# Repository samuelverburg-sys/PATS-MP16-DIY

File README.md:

# PATS MP-16 DIY kit

A 16-pad MIDI chord controller you build yourself: 16 MX pads and a Shift key with RGB lighting, a
rotary encoder, a 128x64 OLED, USB MIDI and 3.5 mm TRS MIDI In and Out. By
[PATS audio](https://patsaudio.com/).

This repository holds rev 2 of the kit and the firmware for both revisions:

| | Rev 1 (original kit) | Rev 2 (this repo) |
|---|---|---|
| MCU | Waveshare RP2040-Zero module | RP2040 on the board, 16 MB flash, USB-C |
| Keys | 4x4 matrix + Shift on its own pin | 3x 74HC165 shift registers: every key on its own input, no ghosting |
| Power | LiPo, MCP73831 charger | LiPo with power path (plays while charging), reverse-polarity protection, battery voltage sense, 5 V LED supply |
| MIDI | TRS In + Out | TRS In + Out (Type A), Thru selectable in the MIDI menu |
| Expansion | 3-pin header | 4-pin I2C connector (JST SH, Qwiic / STEMMA QT pinout) for add-on boards |

The rev 1 manual (printing, assembly, how the Chordmaker works):
[PATS MP-16 DIY Kit Manual](https://docs.google.com/document/d/1Koq2ymRy1WZg_HTG9N3nUoAihR9oNaCTS2vanQYqxgY/).

## Firmware

| Sketch | What it does | USB stack |
|---|---|---|
| `MP16_Chordmaker` | The main firmware: each pad plays a chord in the chosen key and scale | Adafruit TinyUSB |
| `MP16_Boilerplate` | Starting point for your own firmware | Adafruit TinyUSB |
| `MP16_YoutubeKeyboard` | The MP-16 as a USB keyboard for YouTube shortcuts | Pico SDK |

### With the Arduino IDE

1. Install the "Raspberry Pi Pico/RP2040/RP2350" boards (Boards Manager; from
   [arduino-pico](https://github.com/earlephilhower/arduino-pico)).
2. Install the libraries Adafruit NeoPixel, Adafruit SSD1306 and Adafruit GFX (Library Manager).
3. **File > Preferences > Sketchbook location**: the `firmware` folder of this repository. The IDE then
   finds the sketches (File > Sketchbook) and the `MP16` library they share.
4. Pick the board and options:

   | | Rev 1 kit | Rev 2 kit |
   |---|---|---|
   | Board | Waveshare RP2040 Zero | Generic RP2040 |
   | Flash Size | 2MB (Sketch: 1536KB, FS: 512KB) | 16MB (Sketch: 2MB, FS: 14MB) |
   | Boot Stage 2 | (default) | W25Q080 QSPI /2 |
   | USB Stack | as in the table above | as in the table above |

   The firmware picks the right pins from the board you choose.
5. Hold **BOOT**, press and release **RESET**, release BOOT: the MP-16 appears as a drive. Click Upload.

### With the command line

```sh
scripts/setup-arduino.sh        # pinned arduino-cli, RP2040 core and libraries
scripts/build-firmware.sh       # every sketch for both boards: build/<rev>/<sketch>/<sketch>.ino.uf2
make -C firmware/test           # tests of the chord engine, MIDI parser and input logic (needs g++)
```

Copy the `.uf2` onto the MP-16's drive (BOOT + RESET as above) to flash it.

## Hardware

The rev 2 schematic and PCB are generated from `hardware/mp16/design.py` with KiCad 7+ and
Freerouting (`hardware/README.md`). The generated KiCad project and the JLCPCB order files are in
`hardware/mp16/`. The original rev 1 EasyEDA project is in `hardware/reference/`.

## Enclosure

`enclosure/stl/`: Top, Midplate, Bottom (closed or open), Switch and OLED standoff, the same for both
revisions. `enclosure/layout.kle.json` is the key layout for
[keyboard-layout-editor.com](http://www.keyboard-layout-editor.com/).

## Working on this with Claude

`CLAUDE.md` describes the layout, commands and rules; cloud sessions install the toolchain through
`.claude/hooks/session-start.sh`. Other firmware for the kit:
[MP-16 Chordmaker V2](https://github.com/giusmarci/MP16-CHORDMAKER-V2) by @giusmarci.

Questions, builds and ideas: [PATS audio on Instagram](https://www.instagram.com/patsaudio/).

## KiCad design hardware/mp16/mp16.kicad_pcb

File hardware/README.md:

# MP-16 rev 2 hardware

One board, generated from Python and checked by script: `mp16/design.py` is the source of truth for
every part, value, LCSC number, connection and position. The KiCad files in `mp16/` are generated from
it; never edit them by hand (the next build overwrites them).

| | |
|---|---|
| Outline | 76.2 x 104.775 mm, six 2.5 mm holes: the rev-1 board, so the enclosure (`../enclosure/stl/`) fits |
| Layers | 2, JLCPCB standard rules (0.127 mm tracks, 0.13 mm clearance) |
| Assembly | every SMD part on the bottom (one JLCPCB assembly side, as rev 1); 4 layers (In1 GND, In2 VLED; Samuel 2026-11-03: cheaper overall than 2 layers with double-sided assembly); hand-soldered on top: encoder, OLED header |
| Spec and decisions | `../docs/SPEC.md`, `../docs/decisions/` |

## Build

```sh
../scripts/setup-kicad.sh          # KiCad 7, Java 25, Freerouting 2.5.0 (once)
python3 build.py mp16 check        # netlist checks (seconds)
python3 build.py mp16 sch          # schematic + KiCad netlist round trip
python3 build.py mp16 pcb          # placed board + placement checks (courtyards, part drawings, facing, crossing order)
python3 build.py mp16 all          # check, sch, pcb, route, drc, review, fab (about 10 minutes)
python3 tools/where.py mp16 [x0 y0 x1 y1]   # part boxes in the design frame, for placing parts
BOARD=mp16 tools/xray.sh build/xray.png 250 [x0 y0 w h]   # bottom parts seen from above (design frame)
BOARD=mp16 tools/render.sh build   # top and bottom renders
python3 ../scripts/check-pins.py   # firmware pins (board_pins.h) == this board
```

Outputs: `mp16/mp16.kicad_sch`, `mp16/mp16.kicad_pcb`, `mp16/fab/` (Gerbers zip, BOM and CPL for
JLCPCB). Every `route`, `drc` and `review` run adds a line to `build-log.jsonl`.

## Where things are and why

Frame: mm seen from above, (0, 0) = top-left corner, y = 0 is the edge with the jacks (the KLE layout's
frame; the enclosure STLs use the same x and y_stl = 104.775 - y).

- **Fixed by the enclosure** (rev-1 positions, placed by `pin_targets` onto the rev-1 pad centres from
  `reference/rev1-pcb.easyeda.json`, with footprints converted from that board): MIDI In jack (x 19.6),
  USB-C (x 38.1, where the RP2040-Zero's socket was), MIDI Out jack (x 53.9), power switch (x 68.3),
  side-view charge LED, encoder, OLED header. These never move (Samuel, 2026-10-22). The battery plug
  (66.4, 26.7) is at its rev-1 position too, but may move.
  Checked against the STL openings with `tools/stl_openings.py`.
- **Top band (y 0-31)**: RP2040 and its flash and crystal in the middle (inside the window of the "Bottom
  (Open)" shell, with BOOT, RESET and the SWD pads), MIDI In circuit under its jack, charger, load switch,
  LDO and LED level shifter on the right, battery voltage divider and protection beside the battery plug.
  0402 passives here; 0603 elsewhere.
- **Buttons and debug**: BOOT (SW18) and RESET (SW19) side by side in the lower left of the open bottom
  shell's window, named on the bottom silkscreen; above them three SWD pads, TP2 SWDIO, TP1 SWCLK,
  TP3 GND (left to right seen from above, right to left seen from below). Flashing a blank or stuck
  board: hold BOOT, press RESET, release BOOT; the RPI-RP2 drive appears.
- **Key area**: hot-swap sockets, LEDs and their capacitors as the PATS UI board; U1 (pads 1-8) between key
  rows 1 and 2 and U2 (pads 9-16) between rows 3 and 4, next to the keys they read; the 5 V LED boost
  between pads 3 and 4 and along row 1's LEDs.

## JLCPCB (PCB and assembly)

The board is made and assembled at JLCPCB (Samuel, 2026-10-22). Check the numbers below against their
current capabilities page before each order; the build enforces the ones in **bold**.

| Constraint | JLCPCB (4-layer, standard) | This board |
|---|---|---|
| Track width / spacing | 0.127 / 0.127 mm minimum | **0.127 mm min track, 0.13 mm clearance** (router works to 0.15) |
| Vias | 0.3 mm drill / 0.6 mm pad without extra cost (0.2 mm possible at a fee) | **0.3 / 0.6 mm**, 0.4 / 0.8 mm on power |
| Copper to board edge | 0.3 mm | **0.3 mm** |
| Assembly sides | one side is cheapest (two sides = second setup) | **all SMD on the bottom** |
| Parts over the board edge | needs edge rails (JLCPCB adds them, small fee), as rev 1 | jacks, USB-C, power switch overhang the top edge, as rev 1 |
| Fine pitch | 0.4 mm QFN fine; ENIG recommended | RP2040 0.4 mm, BQ24074 0.5 mm, JST SH 1.0 mm |
| Parts library | basic parts free; each extended part type has a setup fee | `mp16/PARTS.md`; prefer basic passives |
| Through-hole | hand-soldered here (cheaper); JLCPCB THT assembly possible | encoder, OLED header, battery plug; USB-C's shell legs are through-hole but it is placed by JLCPCB (in the CPL) |
| Files | Gerber zip, BOM (Comment, Designator, Footprint, LCSC), CPL (Designator, Mid X/Y, Layer, Rotation) | `mp16/fab/` |

## Fit checks still open (before ordering)

1. USB-C height: the RP2040-Zero's socket sat 1 mm lower (on the module's own board); this socket is on
   the main board. The enclosure opening (about 16 x 10 mm) leaves ~0.5 mm above a standard plug. Check
   with the printed Top/Bottom and a real cable.
2. 3D check of the stack (PCB, plate, OLED, battery between board and bottom shell).

## Pipeline

`build.py`, `tools/` and `lib/` are copied from the PATS repository (github.com/samuelverburg-sys/PATS,
`pats-core/hardware/`, commit 3d1c7dc, 2026-10-22); `PATS-PIPELINE.md` lists the changes made here.
The routing approach (Freerouting in stages, then a local finish router and ground stitching) is
described in the PATS hardware README; this board routes the RP2040's 0.4 mm pins and the charger's
power pins first, then power, then everything else.

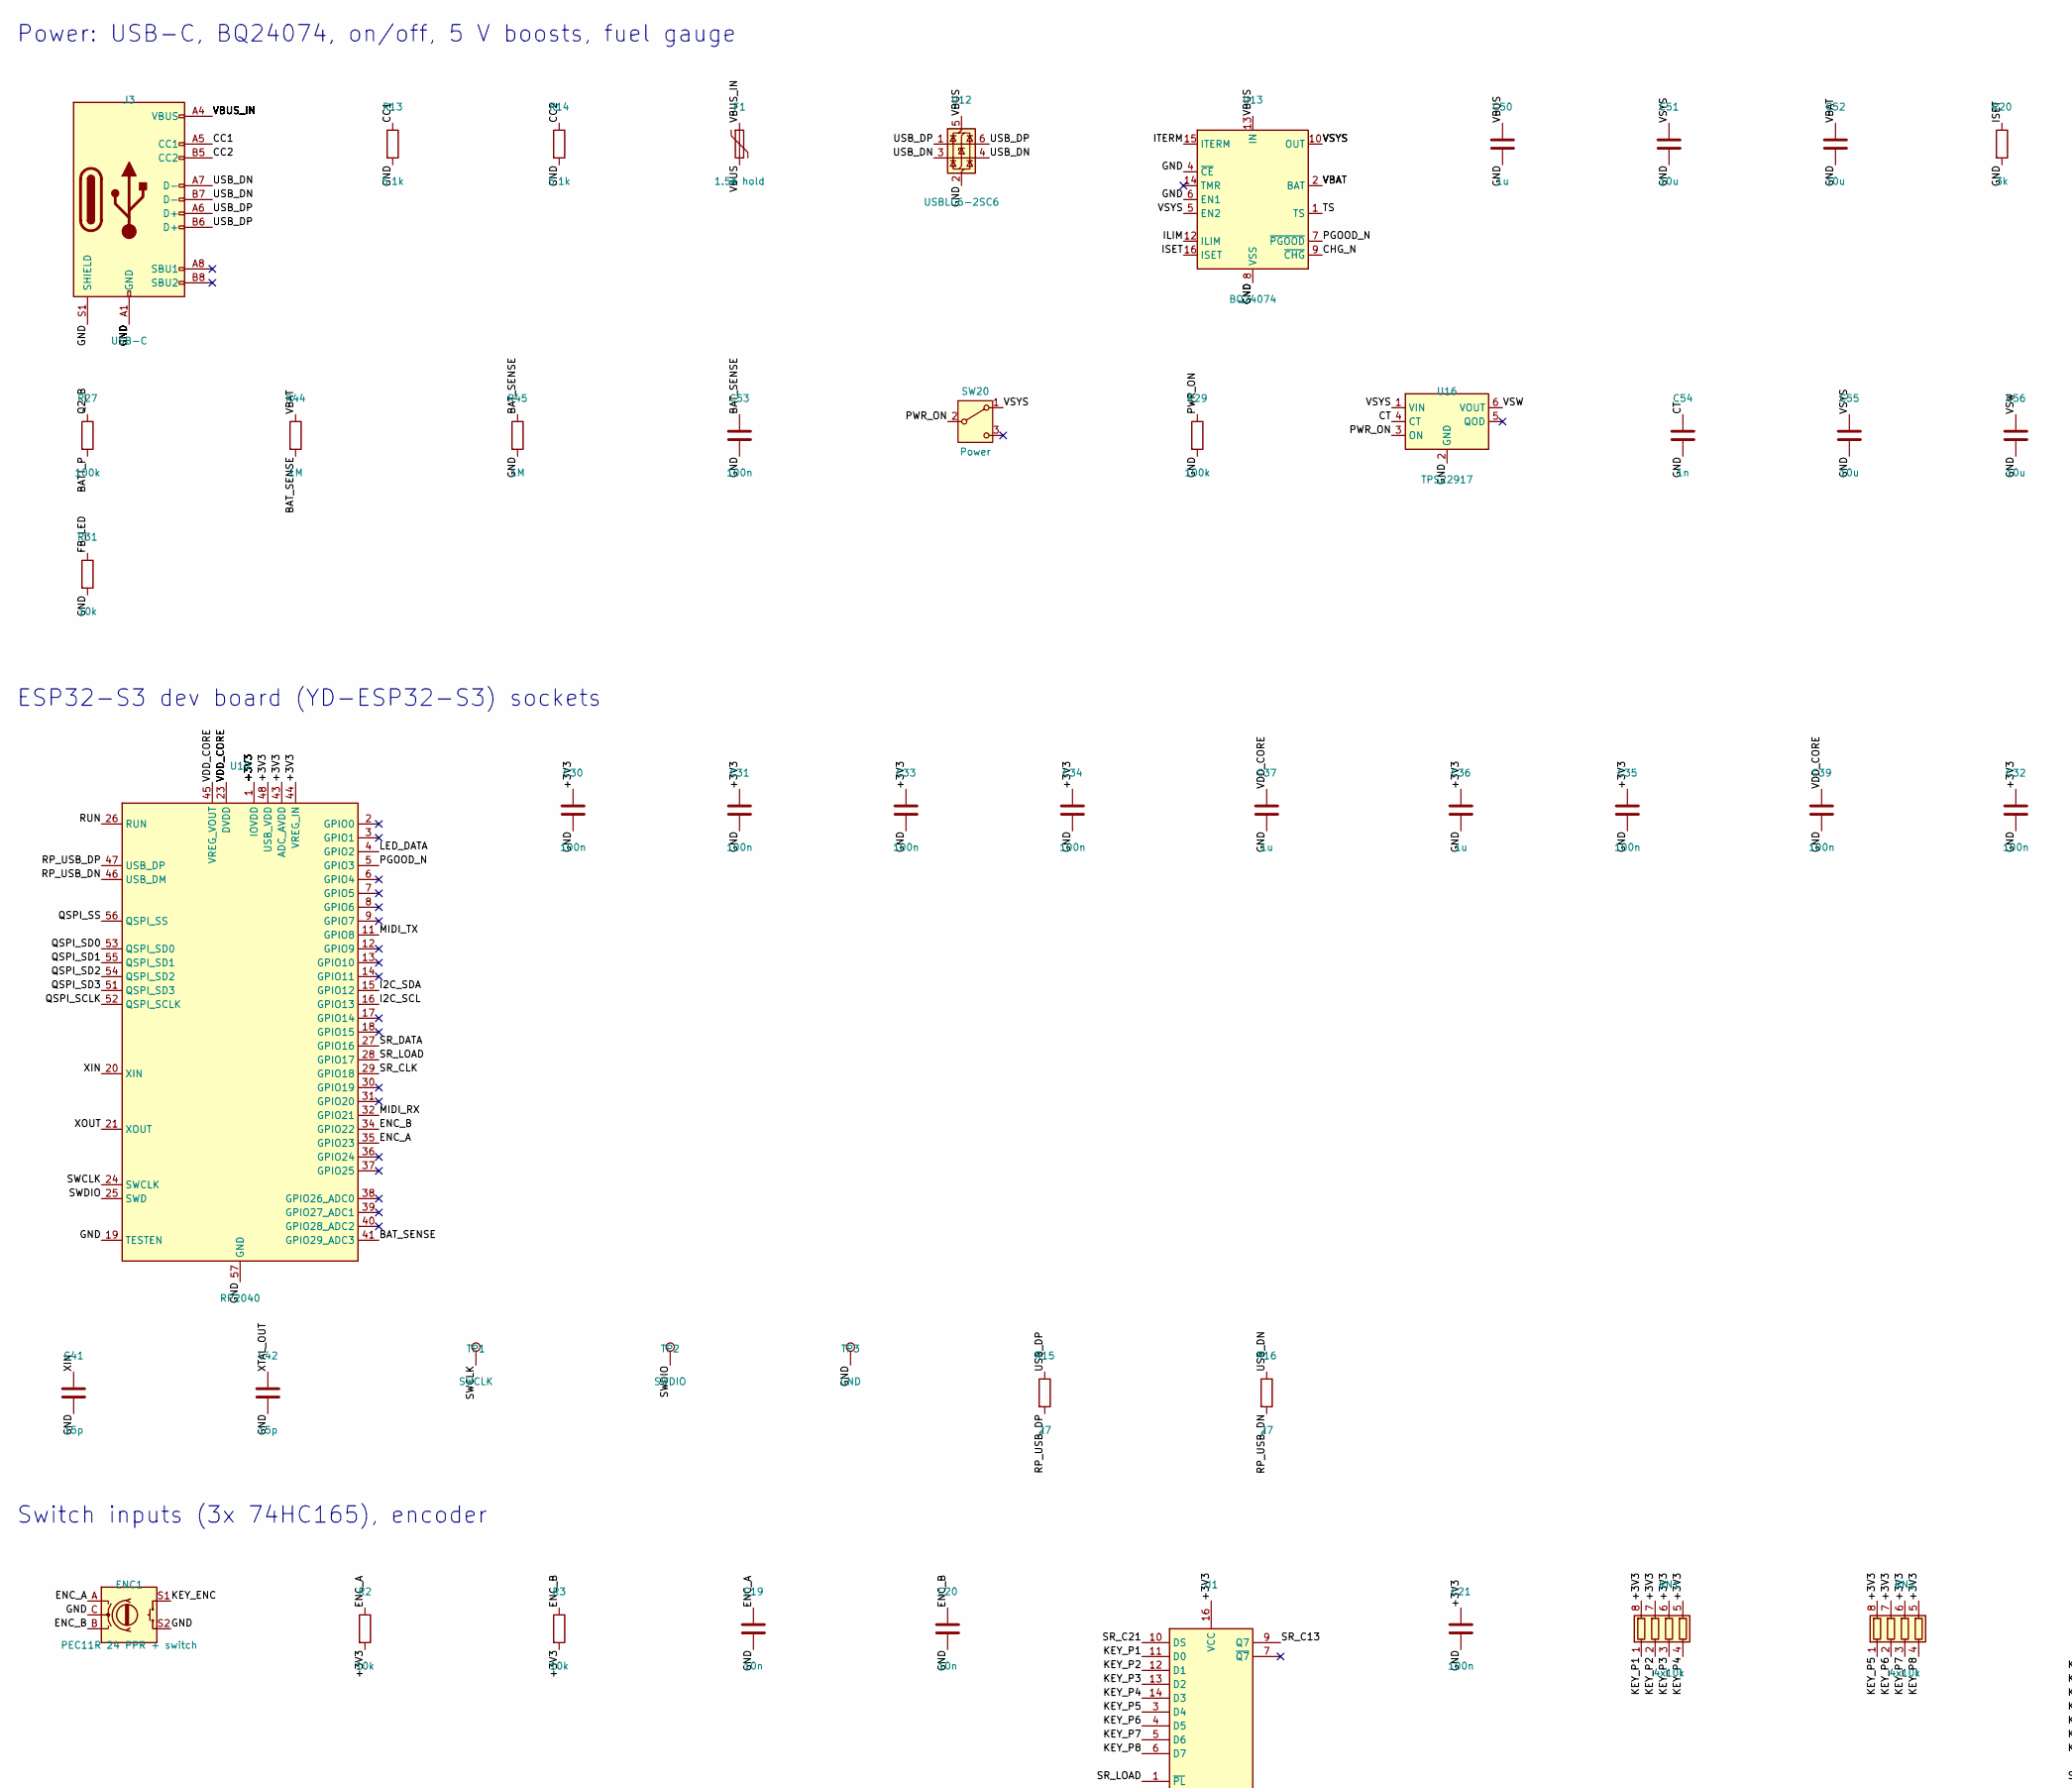
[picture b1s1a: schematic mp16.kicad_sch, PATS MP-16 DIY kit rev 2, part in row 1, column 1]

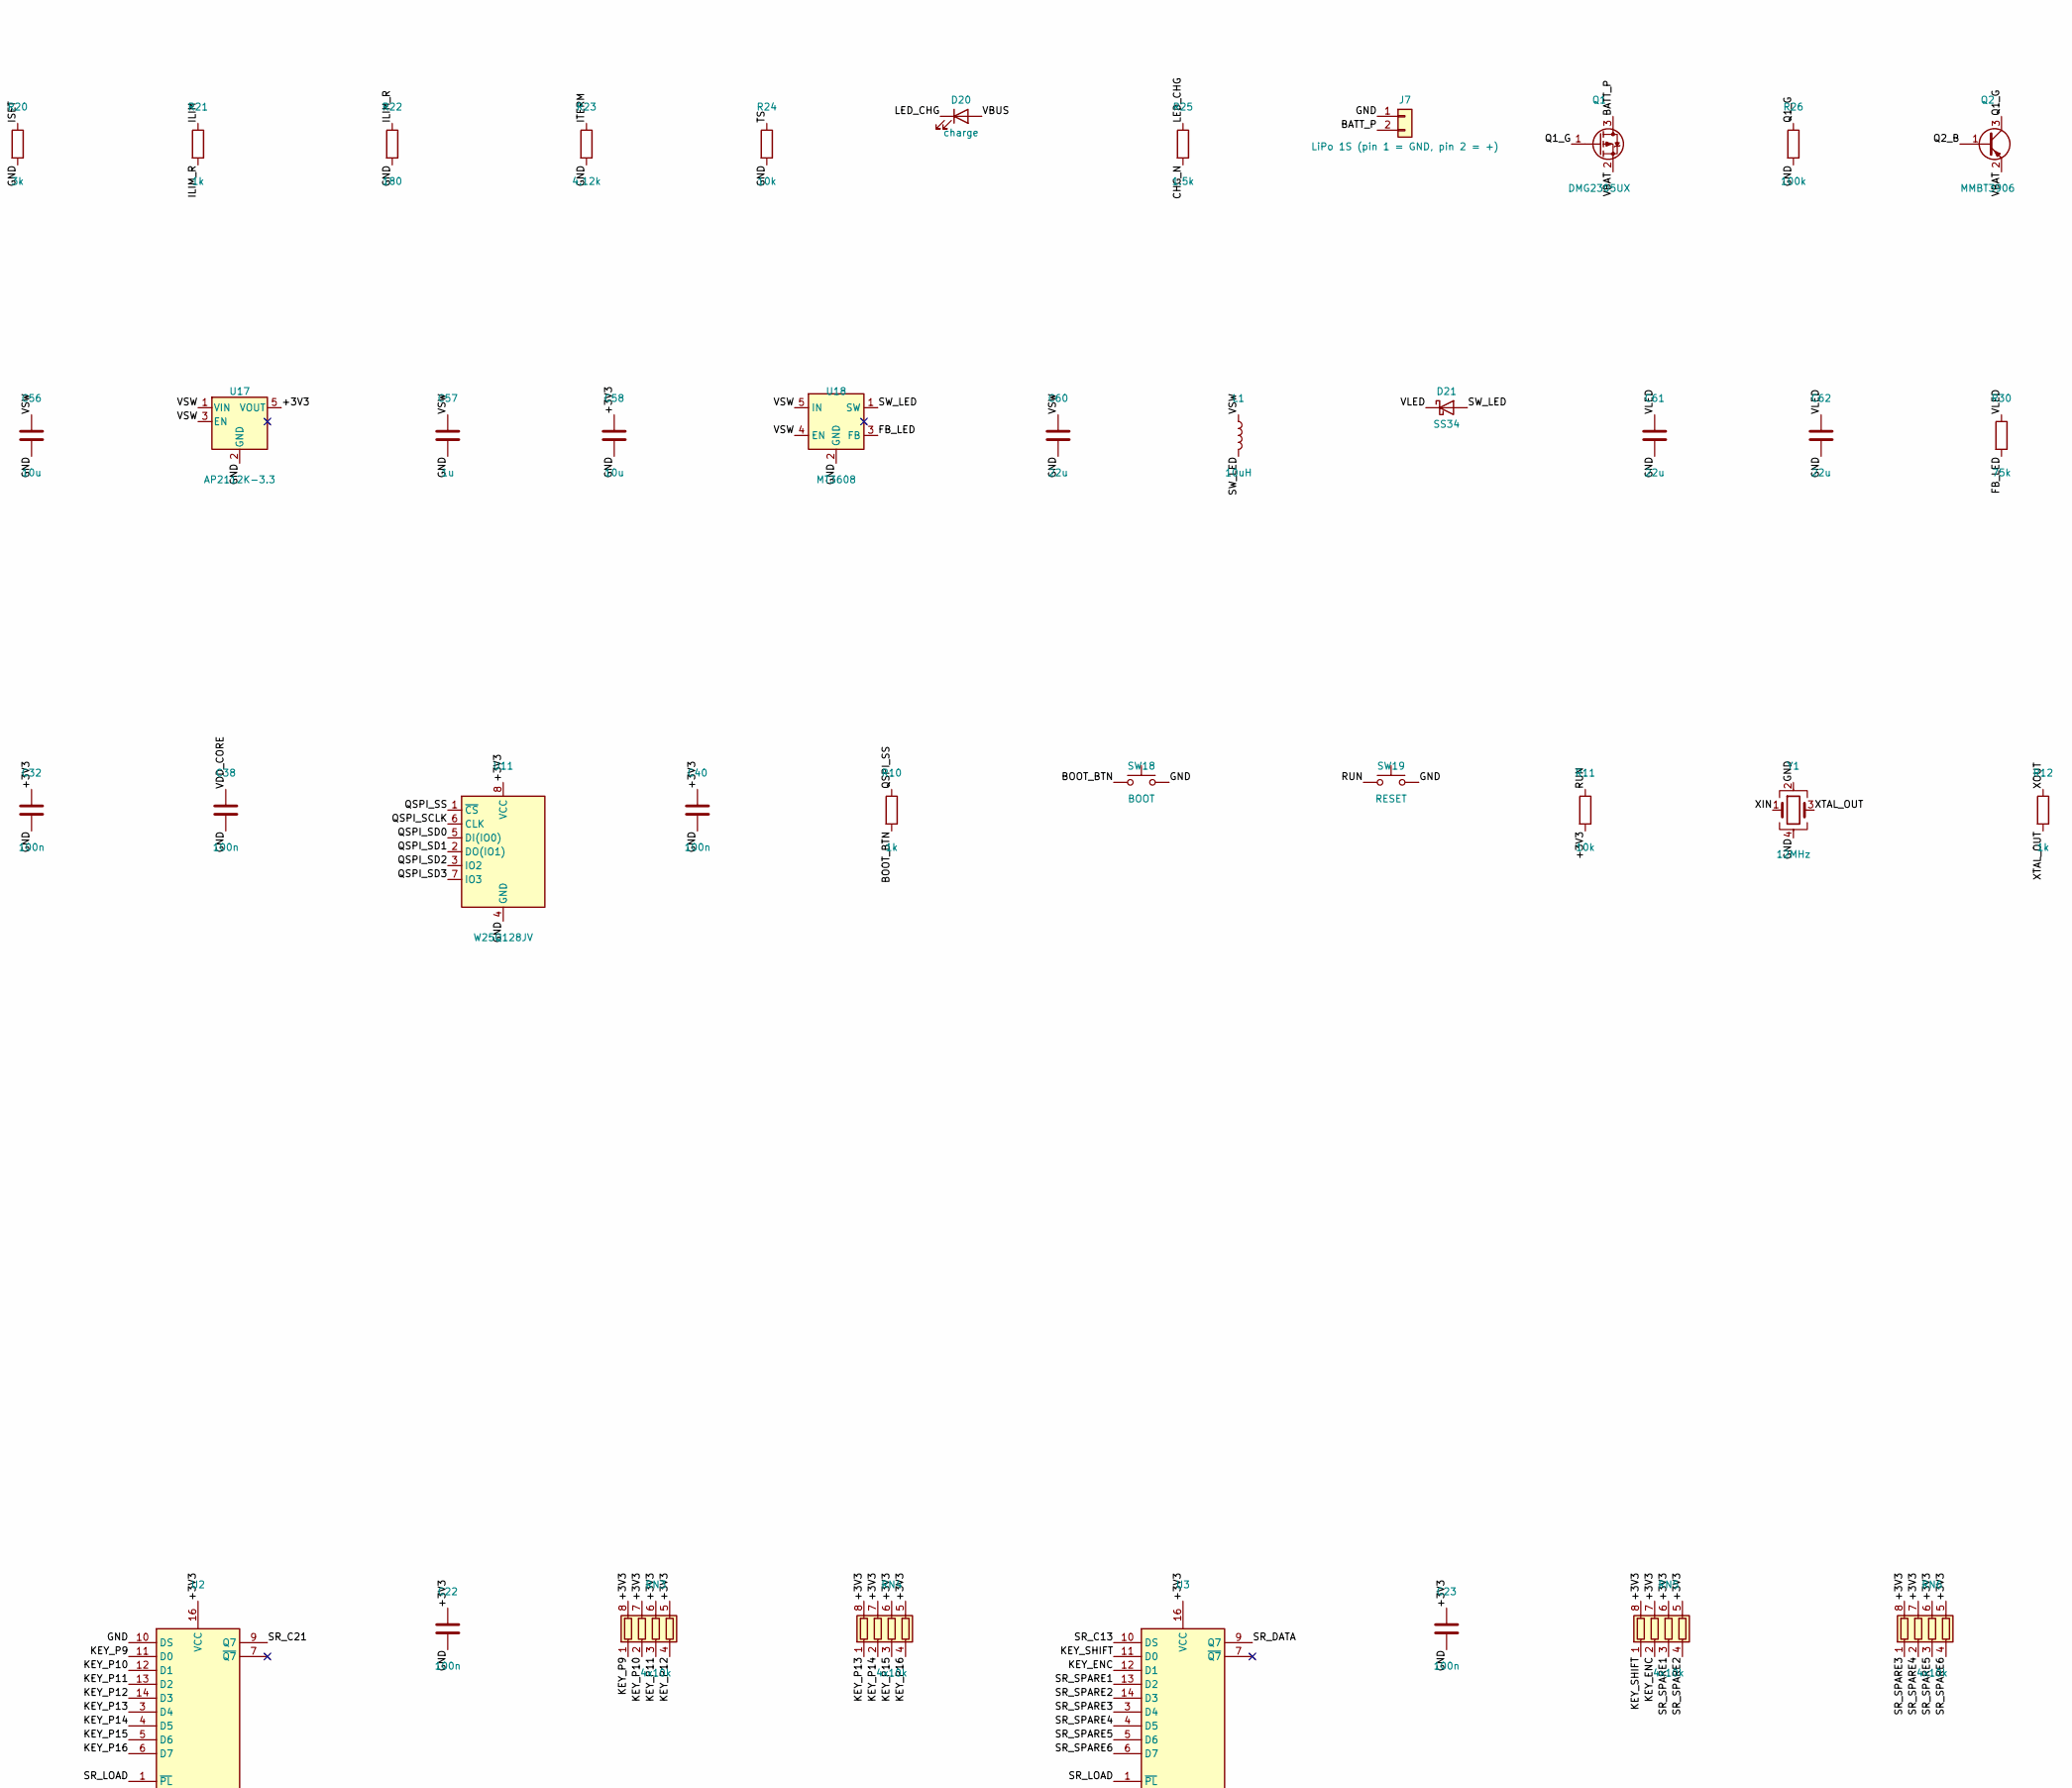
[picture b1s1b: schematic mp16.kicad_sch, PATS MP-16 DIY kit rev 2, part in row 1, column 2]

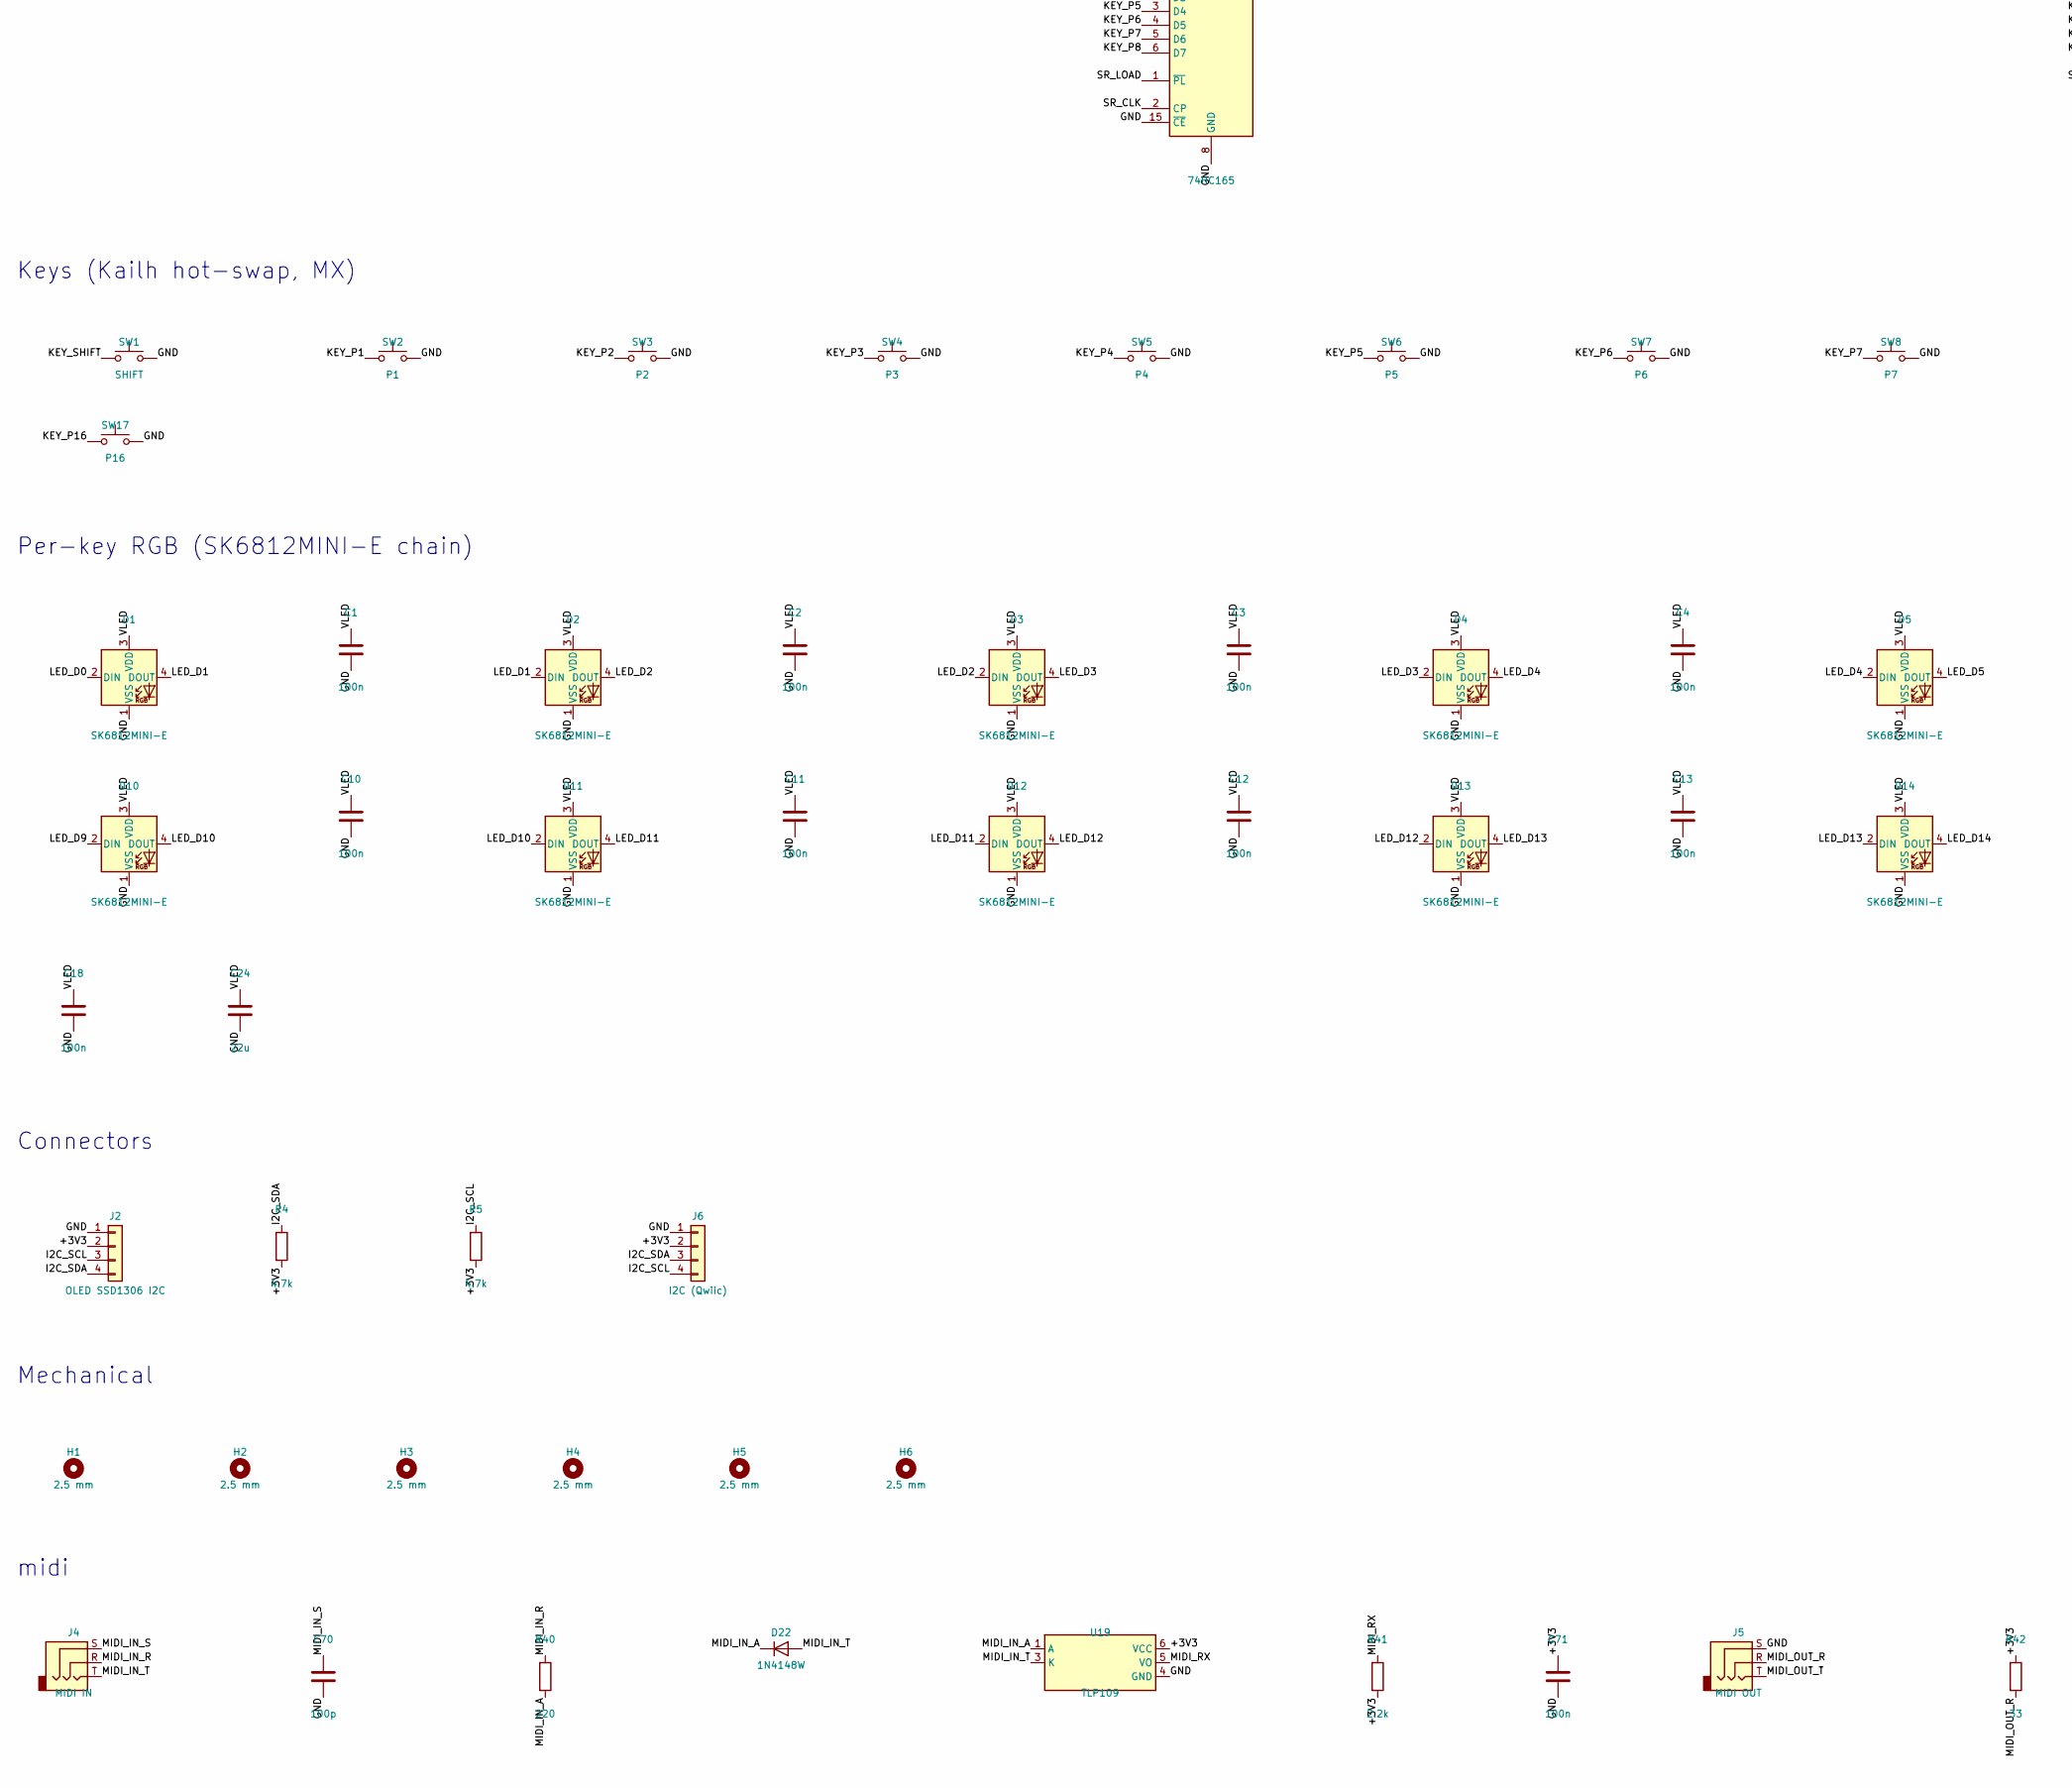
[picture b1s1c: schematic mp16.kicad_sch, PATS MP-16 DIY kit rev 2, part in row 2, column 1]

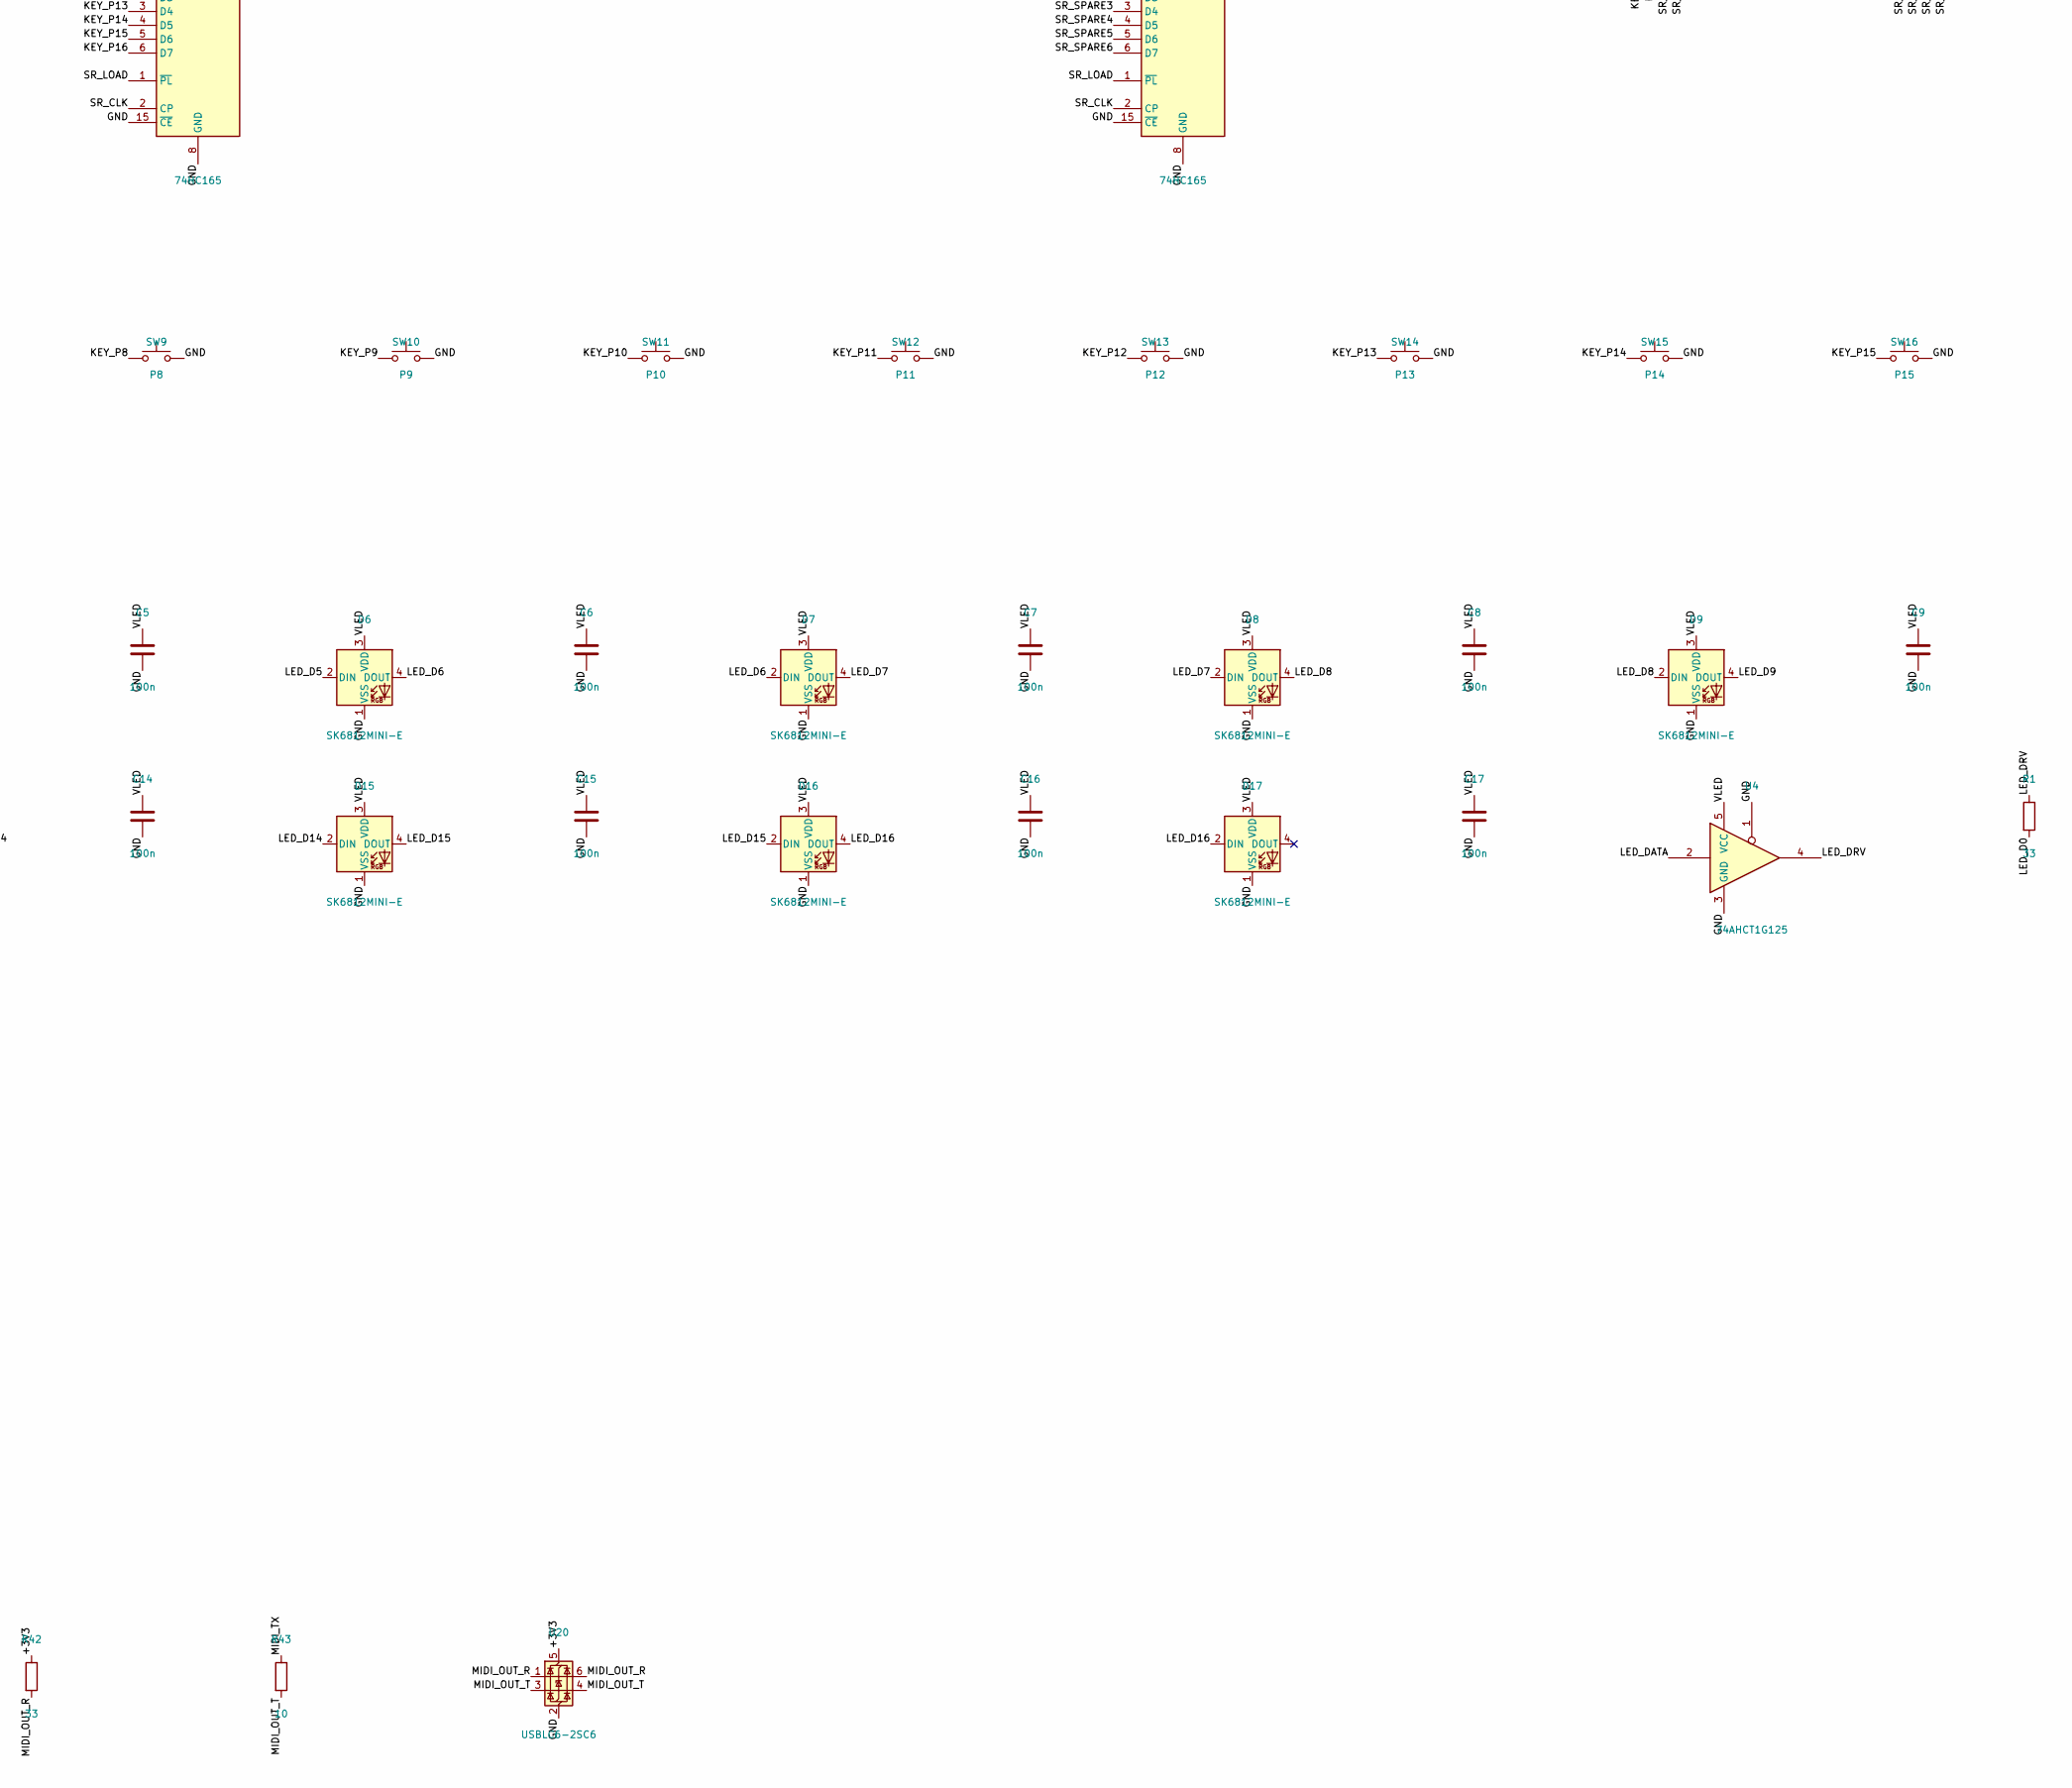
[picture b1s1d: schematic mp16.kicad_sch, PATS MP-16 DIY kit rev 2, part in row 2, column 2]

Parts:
C1, C2, C3, C4, C5, C6, C7, C8, C9, C10, C11, C12, C13, C14, C15, C16, C17, C21, C22, C23: 100n; C_0603_1608Metric
C18, C30, C31, C32, C33, C34, C35, C38, C39, C40, C53, C71: 100n; C_0402_1005Metric
C19, C20: 10n; C_0402_1005Metric
C24, C60, C61, C62: 22u; C_0805_2012Metric
C36, C37, C50, C57: 1u; C_0402_1005Metric
C41, C42: 15p; C_0402_1005Metric
C51, C52, C55, C56, C58: 10u; C_0603_1608Metric; MPN CL10A106MP8NNNC
C54: 1n; C_0402_1005Metric
C70: 100p; C_0402_1005Metric
D1, D2, D3, D4, D5, D6, D7, D8, D9, D10, D11, D12, D13, D14, D15, D16, D17: SK6812MINI-E; LED_SK6812MINI-E_3.2x2.8mm_P1.5mm_ReverseMount; MPN SK6812MINI-E
D20: charge; LED_SideView_XL-1606_RD; MPN XINGLIGHT XL-1606SURC
D21: SS34; D_SMA; MPN SS34
D22: 1N4148W; D_SOD-123; MPN 1N4148W
ENC1: PEC11R 24 PPR + switch; RotaryEncoder_Bourns_PEC11R-4215F-S0024; MPN Bourns PEC11R-4215F-S0024
F1: 1.5A hold; Fuse_1206_3216Metric; MPN 1206 PTC, 1.5 A hold, 6 V
H1, H2, H3, H4, H5, H6: 2.5 mm; MountingHole_2.5mm
J2: OLED SSD1306 I2C; PinSocket_1x04_P2.54mm_Vertical
J3: USB-C; USB_C_Receptacle_HRO_TYPE-C-31-M-12; MPN HRO TYPE-C-31-M-12
J4: MIDI IN; Jack_3.5mm_PJ-320-3P-SMT; MPN PJ-320-3P SMT
J5: MIDI OUT; Jack_3.5mm_PJ-320-3P-SMT; MPN PJ-320-3P SMT
J6: I2C (Qwiic); JST_SH_SM04B-SRSS-TB_1x04-1MP_P1.00mm_Horizontal; MPN JST SM04B-SRSS-TB(LF)(SN)
J7: LiPo 1S (pin 1 = GND, pin 2 = +); JST_PH_S2B-PH-K-S_Horizontal; MPN JST S2B-PH-K-S(LF)(SN)
L1: 10uH; L_Coilcraft_XAL4040-XXX; MPN XAL4040-103MEC
Q1: DMG2305UX; SOT-23; MPN DMG2305UX-7
Q2: MMBT3906; SOT-23; MPN MMBT3906
R1, R42: 33; R_0402_1005Metric
R2, R3, R11, R24, R31: 10k; R_0402_1005Metric
R4, R5: 4.7k; R_0402_1005Metric
R10, R12, R21: 1k; R_0402_1005Metric
R13, R14: 5.1k; R_0402_1005Metric
R15, R16: 27; R_0402_1005Metric
R20: 3k; R_0402_1005Metric
R22: 180; R_0402_1005Metric
R23: 4.12k; R_0603_1608Metric
R25: 1.5k; R_0402_1005Metric
R26, R27, R29: 100k; R_0402_1005Metric
R30: 75k; R_0402_1005Metric
R40: 220; R_0402_1005Metric
R41: 2.2k; R_0402_1005Metric
R43: 10; R_0402_1005Metric
R44, R45: 1M; R_0402_1005Metric
RN1, RN2, RN3, RN4, RN5, RN6: 4x10k; R_Array_Convex_4x0603; MPN 4D03WGJ0103T5E
SW1: SHIFT; MX-Hotswap-1U; MPN Kailh CPG151101S11-16
SW2: P1; MX-Hotswap-1U; MPN Kailh CPG151101S11-16
SW3: P2; MX-Hotswap-1U; MPN Kailh CPG151101S11-16
SW4: P3; MX-Hotswap-1U; MPN Kailh CPG151101S11-16
SW5: P4; MX-Hotswap-1U; MPN Kailh CPG151101S11-16
SW6: P5; MX-Hotswap-1U; MPN Kailh CPG151101S11-16
SW7: P6; MX-Hotswap-1U; MPN Kailh CPG151101S11-16
SW8: P7; MX-Hotswap-1U; MPN Kailh CPG151101S11-16
SW9: P8; MX-Hotswap-1U; MPN Kailh CPG151101S11-16
SW10: P9; MX-Hotswap-1U; MPN Kailh CPG151101S11-16
SW11: P10; MX-Hotswap-1U; MPN Kailh CPG151101S11-16
SW12: P11; MX-Hotswap-1U; MPN Kailh CPG151101S11-16
SW13: P12; MX-Hotswap-1U; MPN Kailh CPG151101S11-16
SW14: P13; MX-Hotswap-1U; MPN Kailh CPG151101S11-16
SW15: P14; MX-Hotswap-1U; MPN Kailh CPG151101S11-16
SW16: P15; MX-Hotswap-1U; MPN Kailh CPG151101S11-16
SW17: P16; MX-Hotswap-1U; MPN Kailh CPG151101S11-16
SW18: BOOT; SW_Push_1P1T_NO_CK_KMR2; MPN C&K KMR221GLFS
SW19: RESET; SW_Push_1P1T_NO_CK_KMR2; MPN C&K KMR221GLFS
SW20: Power; SW_SPDT_MK-12C02-G015; MPN G-Switch MK-12C02-G015
TP1: SWCLK; TestPoint_Pad_D1.0mm
TP2: SWDIO; TestPoint_Pad_D1.0mm
TP3: GND; TestPoint_Pad_D1.0mm
U1, U2, U3: 74HC165; TSSOP-16_4.4x5mm_P0.65mm; MPN 74HC165PW
U4: 74AHCT1G125; SOT-23-5; MPN 74AHCT1G125GV
U10: RP2040; QFN-56-1EP_7x7mm_P0.4mm_EP3.2x3.2mm; MPN RP2040
U11: W25Q128JV; SOIC-8_5.23x5.23mm_P1.27mm; MPN W25Q128JVSIQ
U12, U20: USBLC6-2SC6; SOT-23-6; MPN USBLC6-2SC6
U13: BQ24074; VQFN-16-1EP_3x3mm_P0.5mm_EP1.6x1.6mm; MPN BQ24074RGTR
U16: TPS22917; SOT-23-6; MPN TPS22917DBVR
U17: AP2112K-3.3; SOT-23-5; MPN AP2112K-3.3TRG1
U18: MT3608; SOT-23-6; MPN MT3608
U19: TLP109; Toshiba_SO6-5P_TLP109; MPN TLP109(TPL,E
Y1: 12MHz; Crystal_SMD_3225-4Pin_3.2x2.5mm; MPN Abracon ABM8-272-T3

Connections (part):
+3V3: C21.1, C22.1, C23.1, C30.1, C31.1, C32.1, C33.1, C34.1, C35.1, C36.1, C40.1, C58.1, C71.1, J2.2, J6.2, R2.2, R3.2, R4.2, R5.2, R11.2, R41.2, R42.1, RN1.5 (R4.2), RN1.6 (R3.2), RN1.7 (R2.2), RN1.8 (R1.2), RN2.5 (R4.2), RN2.6 (R3.2), RN2.7 (R2.2), RN2.8 (R1.2), RN3.5 (R4.2), RN3.6 (R3.2), RN3.7 (R2.2), RN3.8 (R1.2), RN4.5 (R4.2), RN4.6 (R3.2), RN4.7 (R2.2), RN4.8 (R1.2), RN5.5 (R4.2), RN5.6 (R3.2), RN5.7 (R2.2), RN5.8 (R1.2), RN6.5 (R4.2), RN6.6 (R3.2), RN6.7 (R2.2), RN6.8 (R1.2), U1.16 (VCC), U2.16 (VCC), U3.16 (VCC), U10.1 (IOVDD), U10.10 (IOVDD), U10.22 (IOVDD), U10.33 (IOVDD), U10.42 (IOVDD), U10.43 (ADC_AVDD), U10.44 (VREG_IN), U10.48 (USB_VDD), U10.49 (IOVDD), U11.8 (VCC), U17.5 (VOUT), U19.6 (VCC), U20.5 (VBUS)
BATT_P: J7.2, Q1.3 (D), R27.2
BAT_SENSE: C53.1, R44.2, R45.1, U10.41 (GPIO29_ADC3)
BOOT_BTN: R10.2, SW18.1
CC1: J3.A5 (CC1), R13.1
CC2: J3.B5 (CC2), R14.1
CHG_N: R25.2, U13.9 (~CHG)
CT: C54.1, U16.4 (CT)
ENC_A: C19.1, ENC1.A, R2.1, U10.35 (GPIO23)
ENC_B: C20.1, ENC1.B, R3.1, U10.34 (GPIO22)
FB_LED: R30.2, R31.1, U18.3 (FB)
GND: C1.2, C2.2, C3.2, C4.2, C5.2, C6.2, C7.2, C8.2, C9.2, C10.2, C11.2, C12.2, C13.2, C14.2, C15.2, C16.2, C17.2, C18.2, C19.2, C20.2, C21.2, C22.2, C23.2, C24.2, C30.2, C31.2, C32.2, C33.2, C34.2, C35.2, C36.2, C37.2, C38.2, C39.2, C40.2, C41.2, C42.2, C50.2, C51.2, C52.2, C53.2, C54.2, C55.2, C56.2, C57.2, C58.2, C60.2, C61.2, C62.2, C70.2, C71.2, D1.1 (VSS), D2.1 (VSS), D3.1 (VSS), D4.1 (VSS), D5.1 (VSS), D6.1 (VSS), D7.1 (VSS), D8.1 (VSS), D9.1 (VSS), D10.1 (VSS), D11.1 (VSS), D12.1 (VSS), D13.1 (VSS), D14.1 (VSS), D15.1 (VSS), D16.1 (VSS), D17.1 (VSS), ENC1.C, ENC1.MP, ENC1.S2, J2.1, J3.A1 (GND), J3.A12 (GND), J3.B1 (GND), J3.B12 (GND), J3.S1 (SHIELD), J5.S, J6.1, J6.MP, J7.1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
I2C_SCL: J2.3, J6.4, R5.1, U10.16 (GPIO13)
I2C_SDA: J2.4, J6.3, R4.1, U10.15 (GPIO12)
ILIM: R21.1, U13.12 (ILIM)
ILIM_R: R21.2, R22.1
ISET: R20.1, U13.16 (ISET)
ITERM: R23.1, U13.15 (ITERM)
KEY_ENC: ENC1.S1, RN5.2 (R2.1), U3.12 (D1)
KEY_P1: RN1.1 (R1.1), SW2.1, U1.11 (D0)
KEY_P2: RN1.2 (R2.1), SW3.1, U1.12 (D1)
KEY_P3: RN1.3 (R3.1), SW4.1, U1.13 (D2)
KEY_P4: RN1.4 (R4.1), SW5.1, U1.14 (D3)
KEY_P5: RN2.1 (R1.1), SW6.1, U1.3 (D4)
KEY_P6: RN2.2 (R2.1), SW7.1, U1.4 (D5)
KEY_P7: RN2.3 (R3.1), SW8.1, U1.5 (D6)
KEY_P8: RN2.4 (R4.1), SW9.1, U1.6 (D7)
KEY_P9: RN3.1 (R1.1), SW10.1, U2.11 (D0)
KEY_P10: RN3.2 (R2.1), SW11.1, U2.12 (D1)
KEY_P11: RN3.3 (R3.1), SW12.1, U2.13 (D2)
KEY_P12: RN3.4 (R4.1), SW13.1, U2.14 (D3)
KEY_P13: RN4.1 (R1.1), SW14.1, U2.3 (D4)
KEY_P14: RN4.2 (R2.1), SW15.1, U2.4 (D5)
KEY_P15: RN4.3 (R3.1), SW16.1, U2.5 (D6)
KEY_P16: RN4.4 (R4.1), SW17.1, U2.6 (D7)
KEY_SHIFT: RN5.1 (R1.1), SW1.1, U3.11 (D0)
LED_CHG: D20.1 (K), R25.1
LED_D0: D1.2 (DIN), R1.2
LED_D1: D1.4 (DOUT), D2.2 (DIN)
LED_D2: D2.4 (DOUT), D3.2 (DIN)
LED_D3: D3.4 (DOUT), D4.2 (DIN)
LED_D4: D4.4 (DOUT), D5.2 (DIN)
LED_D5: D5.4 (DOUT), D6.2 (DIN)
LED_D6: D6.4 (DOUT), D7.2 (DIN)
LED_D7: D7.4 (DOUT), D8.2 (DIN)
LED_D8: D8.4 (DOUT), D9.2 (DIN)
LED_D9: D9.4 (DOUT), D10.2 (DIN)
LED_D10: D10.4 (DOUT), D11.2 (DIN)
LED_D11: D11.4 (DOUT), D12.2 (DIN)
LED_D12: D12.4 (DOUT), D13.2 (DIN)
LED_D13: D13.4 (DOUT), D14.2 (DIN)
LED_D14: D14.4 (DOUT), D15.2 (DIN)
LED_D15: D15.4 (DOUT), D16.2 (DIN)
LED_D16: D16.4 (DOUT), D17.2 (DIN)
LED_DATA: U4.2, U10.4 (GPIO2)
LED_DRV: R1.1, U4.4
MIDI_IN_A: D22.1 (K), R40.2, U19.1 (A)
MIDI_IN_R: J4.R, R40.1
MIDI_IN_S: C70.1, J4.S
MIDI_IN_T: D22.2 (A), J4.T, U19.3 (K)
MIDI_OUT_R: J5.R, R42.2, U20.1 (I/O1), U20.6 (I/O1)
MIDI_OUT_T: J5.T, R43.2, U20.3 (I/O2), U20.4 (I/O2)
MIDI_RX: R41.1, U10.32 (GPIO21), U19.5 (VO)
MIDI_TX: R43.1, U10.11 (GPIO8)
PGOOD_N: U10.5 (GPIO3), U13.7 (~PGOOD)
PWR_ON: R29.1, SW20.2 (B), U16.3 (ON)
Q1_G: Q1.1 (G), Q2.3 (C), R26.1
Q2_B: Q2.1 (B), R27.1
QSPI_SCLK: U10.52 (QSPI_SCLK), U11.6 (CLK)
QSPI_SD0: U10.53 (QSPI_SD0), U11.5 (DI(IO0))
QSPI_SD1: U10.55 (QSPI_SD1), U11.2 (DO(IO1))
QSPI_SD2: U10.54 (QSPI_SD2), U11.3 (IO2)
QSPI_SD3: U10.51 (QSPI_SD3), U11.7 (IO3)
QSPI_SS: R10.1, U10.56 (QSPI_SS), U11.1 (~CS)
RP_USB_DN: R16.2, U10.46 (USB_DM)
RP_USB_DP: R15.2, U10.47 (USB_DP)
RUN: R11.1, SW19.1, U10.26 (RUN)
SR_C13: U1.9 (Q7), U3.10 (DS)
SR_C21: U1.10 (DS), U2.9 (Q7)
SR_CLK: U1.2 (CP), U2.2 (CP), U3.2 (CP), U10.29 (GPIO18)
SR_DATA: U3.9 (Q7), U10.27 (GPIO16)
SR_LOAD: U1.1 (~PL), U2.1 (~PL), U3.1 (~PL), U10.28 (GPIO17)
SR_SPARE1: RN5.3 (R3.1), U3.13 (D2)
SR_SPARE2: RN5.4 (R4.1), U3.14 (D3)
SR_SPARE3: RN6.1 (R1.1), U3.3 (D4)
SR_SPARE4: RN6.2 (R2.1), U3.4 (D5)
SR_SPARE5: RN6.3 (R3.1), U3.5 (D6)
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
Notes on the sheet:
Power: USB-C, BQ24074, on/off, 5 V boosts, fuel gauge
ESP32-S3 dev board (YD-ESP32-S3) sockets
Switch inputs (3x 74HC165), encoder
Keys (Kailh hot-swap, MX)
Per-key RGB (SK6812MINI-E chain)
Connectors
Mechanical
midi
